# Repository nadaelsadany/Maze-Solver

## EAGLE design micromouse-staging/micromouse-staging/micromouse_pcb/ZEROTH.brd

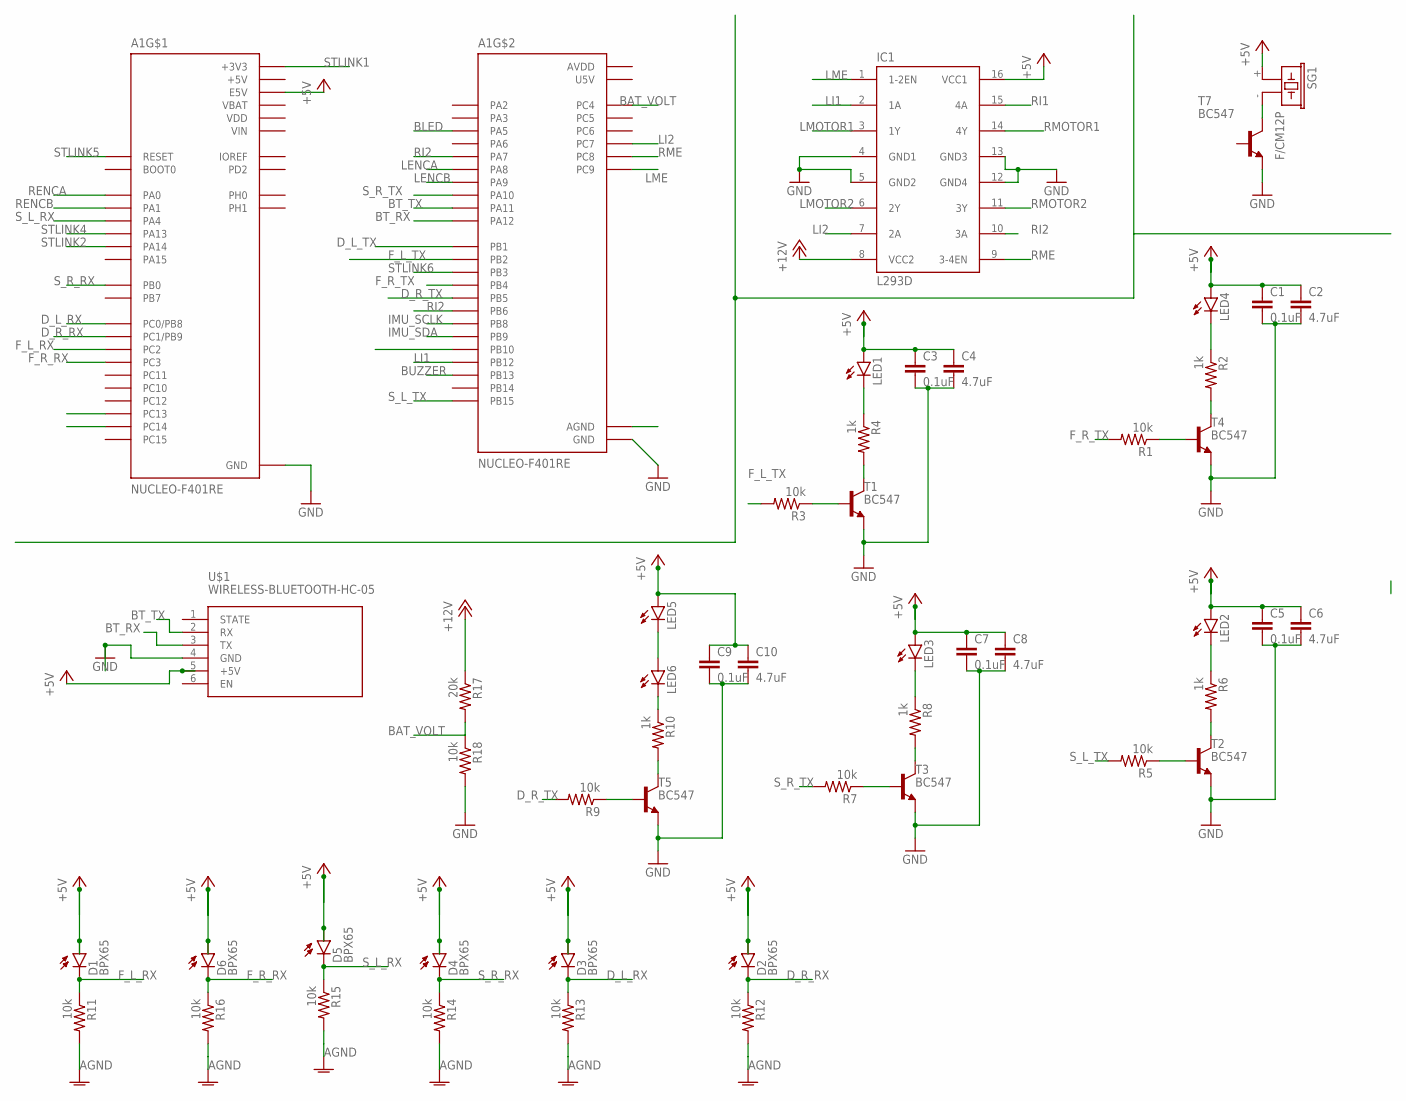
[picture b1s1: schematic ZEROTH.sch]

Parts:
A1: NUCLEO-F401RE; ST_NUCLEO-F401RE
C1, C3, C5, C7, C9: 0.1uF; C2.5-3
C2, C4, C6, C8, C10: 4.7uF; C2.5-3
D1, D2, D3, D4, D5, D6: BPX65
IC1: L293D; DIL16
LED1, LED2, LED3, LED4, LED5, LED6: LED5MM
R1, R3, R5, R7, R9, R11, R12, R13, R14, R15, R16, R18: 10k; 0204/7
R2, R4, R6, R8, R10: 1k; 0204/7
R17: 20k; 0204/7
SG1: F/CM12P
T1, T2, T3, T4, T5, T7: BC547; TO92
U$1: WIRELESS-BLUETOOTH-HC-05

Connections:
+3V3: A1.CN6_4 (+3V3)
+5V: A1.CN6_5 (+5V), A1.CN7_6 (E5V), A1.CN7_18 (+5V), C1.1, C2.1, C3.1, C4.1, C5.1, C6.1, C7.1, C8.1, C9.1, C10.1, D1.A, D2.A, D3.A, D4.A, D5.A, D6.A, IC1.16 (VCC1), LED1.A, LED2.A, LED3.A, LED4.A, LED5.A, SG1.+ (1), U$1.5 (+5V)
+12V: IC1.8 (VCC2), R17.1
AGND: A1.CN10_32 (AGND), R11.2, R12.2, R13.2, R14.2, R15.2, R16.2
AREF: A1.CN5_8 (AREF)
AVDD: A1.CN10_7 (AVDD)
BAT_VOLT: A1.CN10_34 (PC4), R17.2, R18.1
BLED: A1.CN10_11 (PA5)
BT_RX: A1.CN10_12 (PA12), U$1.3 (TX)
BT_TX: A1.CN10_14 (PA11), U$1.2 (RX)
BUZZER: A1.CN10_30 (PB13)
D_L_RX: A1.CN7_38 (PC0/PB8), D3.K (C), R13.1
D_L_TX: A1.CN10_24 (PB1)
D_R_RX: A1.CN7_36 (PC1/PB9), D2.K (C), R12.1
D_R_TX: A1.CN10_29 (PB5), R9.2
F_L_RX: A1.CN7_35 (PC2), D1.K (C), R11.1
F_L_TX: A1.CN10_22 (PB2), R3.2
F_R_RX: A1.CN7_37 (PC3), D6.K (C), R16.1
F_R_TX: A1.CN10_27 (PB4), R1.2
GND: A1.CN5_7 (GND), A1.CN6_6 (GND), A1.CN6_7 (GND), A1.CN7_8 (GND), A1.CN7_19 (GND), A1.CN7_20 (GND), A1.CN7_22 (GND), A1.CN10_9 (GND), A1.CN10_20 (GND), C1.2, C2.2, C3.2, C4.2, C5.2, C6.2, C7.2, C8.2, C9.2, C10.2, IC1.4 (GND1), IC1.5 (GND2), IC1.12 (GND4), IC1.13 (GND3), R18.2, T1.1 (E), T2.1 (E), T3.1 (E), T4.1 (E), T5.1 (E), T7.1 (E), U$1.4 (GND)
IMU_SCLK: A1.CN10_3 (PB8)
IMU_SDA: A1.CN10_5 (PB9)
LENCA: A1.CN10_23 (PA8)
LENCB: A1.CN10_21 (PA9)
LI1: A1.CN10_16 (PB12), IC1.2 (1A)
LI2: A1.CN10_19 (PC7), IC1.7 (2A)
LME: A1.CN10_1 (PC9), IC1.1 (1-2EN)
LMOTOR1: IC1.3 (1Y)
LMOTOR2: IC1.6 (2Y)
unnamed: SG1.- (2), T7.3 (C)
unnamed: R1.1, T4.2 (B)
unnamed: LED4.K (C), R2.1
unnamed: R2.2, T4.3 (C)
unnamed: R5.1, T2.2 (B)
unnamed: R3.1, T1.2 (B)
unnamed: LED1.K (C), R4.1
unnamed: R4.2, T1.3 (C)
unnamed: LED2.K (C), R6.1
unnamed: R6.2, T2.3 (C)
unnamed: R7.1, T3.2 (B)
unnamed: LED3.K (C), R8.1
unnamed: R8.2, T3.3 (C)
unnamed: R9.1, T5.2 (B)
unnamed: LED5.K (C), LED6.A
unnamed: R10.2, T5.3 (C)
unnamed: LED6.K (C), R10.1
RENCA: A1.CN7_28 (PA0)
RENCB: A1.CN7_30 (PA1)
RI1: IC1.15 (4A)
RI2: A1.CN10_15 (PA7), A1.CN10_17 (PB6), IC1.10 (3A)
RME: A1.CN10_2 (PC8), IC1.9 (3-4EN)
RMOTOR1: IC1.14 (4Y)
RMOTOR2: IC1.11 (3Y)
STLINK1: A1.CN7_16 (+3V3)
STLINK2: A1.CN7_15 (PA14)
STLINK4: A1.CN7_13 (PA13)
STLINK5: A1.CN7_14 (RESET)
STLINK6: A1.CN10_31 (PB3)
S_L_RX: A1.CN7_32 (PA4), D5.K (C), R15.1
S_L_TX: A1.CN10_26 (PB15), R5.2
S_R_RX: A1.CN7_34 (PB0), D4.K (C), R14.1
S_R_TX: A1.CN10_33 (PA10), R7.2
U5V: A1.CN10_8 (U5V)
VBAT: A1.CN7_33 (VBAT)
VDD: A1.CN7_5 (VDD)
VIN: A1.CN6_8 (VIN), A1.CN7_24 (VIN)

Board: 2 copper layers, 50 parts (0 on the bottom side), 41 nets, no tracks yet.

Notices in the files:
parts and their libraries:
diy-modules: Released under the Creative Commons Attribution 4.0 International License: http://creativecommons.org/licenses/by/4.0
